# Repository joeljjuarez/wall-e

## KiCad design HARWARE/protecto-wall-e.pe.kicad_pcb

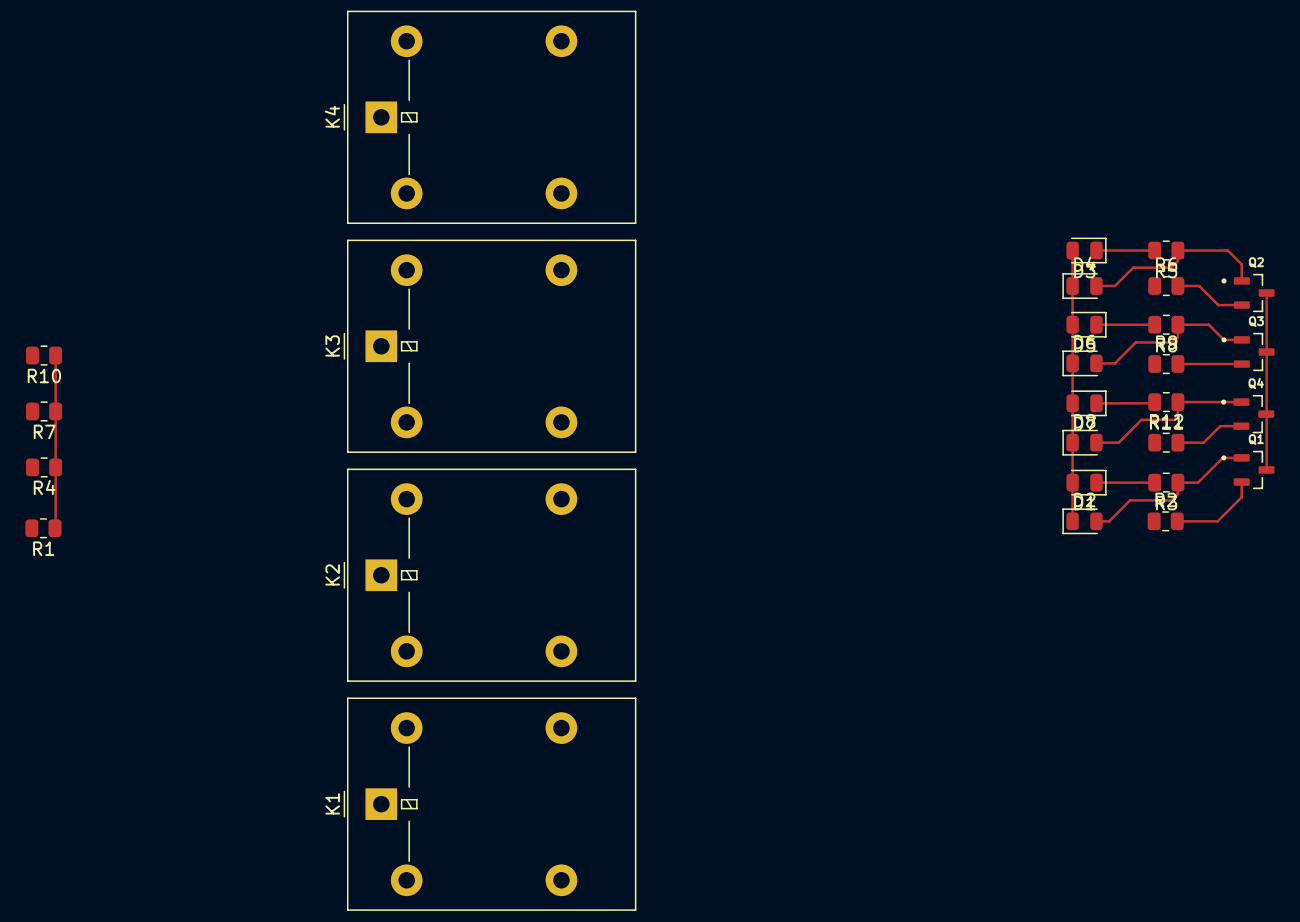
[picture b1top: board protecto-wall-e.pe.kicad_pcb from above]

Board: 2 copper layers, 28 parts (0 on the bottom side), 15 nets.

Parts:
D1, D3, D5, D7: LED; LED_0805_2012Metric
D2, D4, D6, D8: 1N4007; D_0805_2012Metric
K1, K2, K3, K4: SRD-05VDC-SL-C; Relay_SPDT_Omron-G5LE-1
Q1, Q2, Q3, Q4: BC547; SOT95P230X110-3N
R1, R4, R7, R10: 220K; R_0805_2012Metric
R2, R6, R9, R12: 1K; R_0805_2012Metric
R3, R5, R8, R11: 220; R_0805_2012Metric

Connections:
+5V: D1.2 (A), D2.1 (K), D3.2 (A), D4.1 (K), D5.2 (A), D6.1 (K), D7.2 (A), D8.1 (K)
GND: Q1.3 (E), Q2.3 (E), Q3.3 (E), Q4.3 (E)
INPUT: R1.1, R4.1, R7.1, R10.1
unnamed: D1.1 (K), R3.2
unnamed: D2.2 (A), Q1.1 (C), R3.1
unnamed: D3.1 (K), R5.2
unnamed: D4.2 (A), Q2.1 (C), R5.1
unnamed: D5.1 (K), R8.2
unnamed: D6.2 (A), Q3.1 (C), R8.1
unnamed: D7.1 (K), R11.2
unnamed: D8.2 (A), Q4.1 (C), R11.1
unnamed: Q1.2 (B), R2.2
unnamed: Q2.2 (B), R6.2
unnamed: Q3.2 (B), R9.2
unnamed: Q4.2 (B), R12.2

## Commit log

2025-05-07 Kicad agregado
2025-05-07 SOFTWARE agregado
2025-05-07 agregar 3D
